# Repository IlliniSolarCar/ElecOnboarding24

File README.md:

# ElecOnboarding25
This is used for Electrical Onboarding for the Fall 2025 Semester

We are very excited to get to work with you guys!

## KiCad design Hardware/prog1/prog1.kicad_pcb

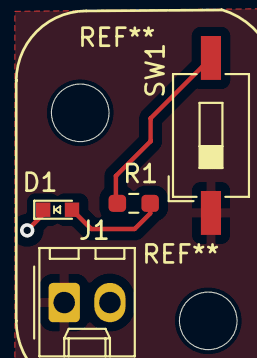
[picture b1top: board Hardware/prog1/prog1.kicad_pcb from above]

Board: 2 copper layers, 4 parts (0 on the bottom side), 4 nets.

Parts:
D1: RED_LED; LED_0603_Symbol_on_F.SilkS
J1: Conn_01x02_Pin; Molex_KK-254_AE-6410-02A_1x02_P2.54mm_Vertical
R1: 105; R_0603_1608Metric_Pad0.98x0.95mm_HandSolder
SW1: SW_Push; SW_DIP_SPSTx01_Slide_6.7x4.1mm_W8.61mm_P2.54mm_LowProfile

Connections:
+3V3: J1.1, SW1.1
GND: D1.1 (K), J1.2
unnamed: D1.2 (A), R1.1
unnamed: R1.2, SW1.2

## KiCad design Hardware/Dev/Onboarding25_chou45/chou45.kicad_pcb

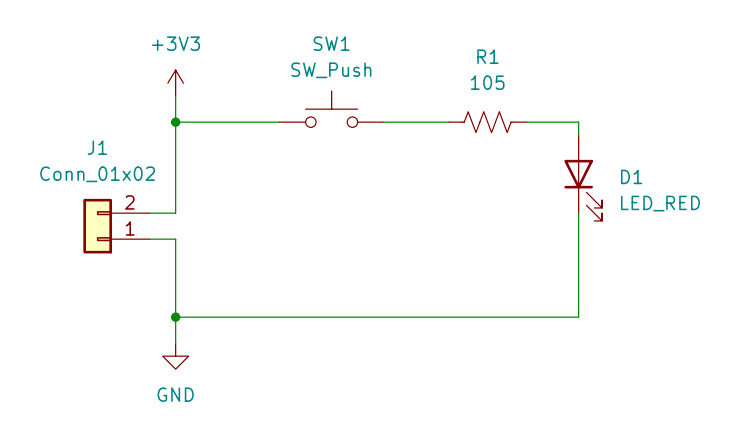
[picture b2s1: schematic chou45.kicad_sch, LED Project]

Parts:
D1: LED_RED; LED_0603_Symbol_on_F.SilkS
J1: Conn_01x02; Molex_KK-254_AE-6410-02A_1x02_P2.54mm_Vertical; MPN 022272021
R1: 105; R_0603_1608Metric_Pad0.98x0.95mm_HandSolder
SW1: SW_Push; SW_DIP_SPSTx01_Slide_6.7x4.1mm_W8.61mm_P2.54mm_LowProfile; MPN 1825910-6

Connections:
+3V3: J1.2, SW1.1
GND: D1.1 (K), J1.1
unnamed: D1.2 (A), R1.2
unnamed: R1.1, SW1.2

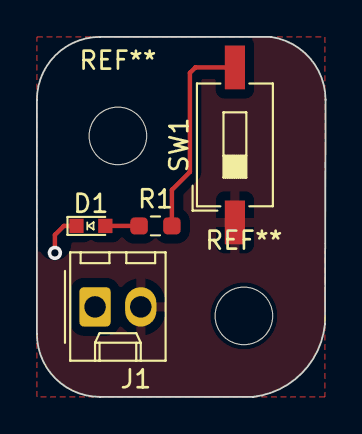
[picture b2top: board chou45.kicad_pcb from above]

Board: 2 copper layers, 16.0 x 20.0 mm, 4 parts (0 on the bottom side), 4 nets.

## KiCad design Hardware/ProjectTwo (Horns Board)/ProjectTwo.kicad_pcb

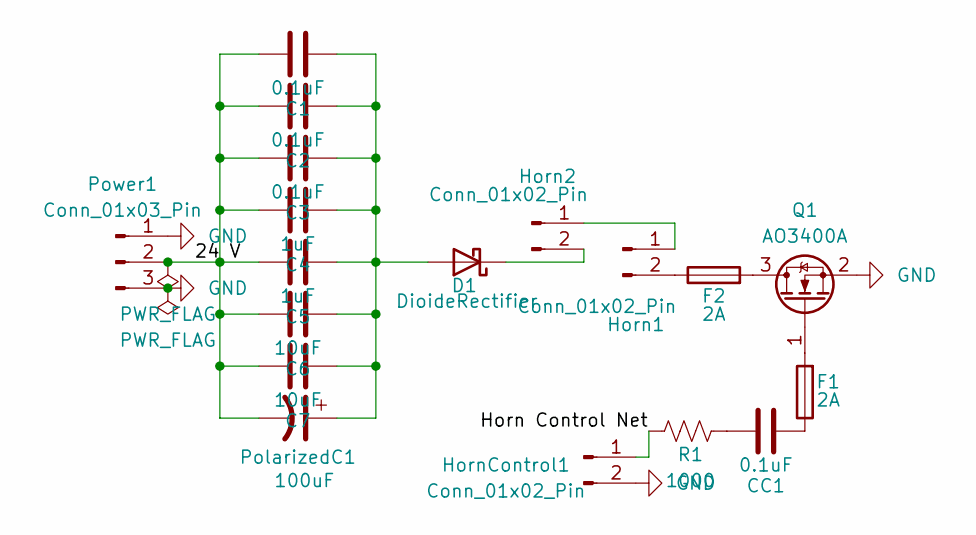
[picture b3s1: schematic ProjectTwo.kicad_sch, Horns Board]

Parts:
C1, C2, C3: 0.1uF; C_1206_3216Metric
C4, C5: 1uF; C_1206_3216Metric
C6, C7: 10uF; C_1206_3216Metric
CC1: 0.1uF; C_1206_3216Metric
D1: DioideRectifier; D_SMA
F1, F2: 2A; Fuse_1206_3216Metric
Horn1, Horn2: Conn_01x02_Pin; TerminalBlock_bornier-2_P5.08mm; MPN CPS-5449-105PM
HornControl1: Conn_01x02_Pin; TerminalBlock_bornier-2_P5.08mm; MPN CPS-5449-105PM
PolarizedC1: 100uF; CP_Radial_D6.3mm_P2.50mm
Power1: Conn_01x03_Pin; TerminalBlock_bornier-3_P5.08mm
Q1: AO3400A; SOT-23; MPN AO3400A
R1: 1000; R_0805_2012Metric

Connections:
/24 V: C1.1, C2.1, C3.1, C4.1, C5.1, C6.1, C7.1, PolarizedC1.2, Power1.2
/Horn Control Net: HornControl1.1, R1.2
GND: HornControl1.2, Power1.1, Power1.3, Q1.2 (S)
unnamed: CC1.1, R1.1
unnamed: CC1.2, F1.1
unnamed: C1.2, C2.2, C3.2, C4.2, C5.2, C6.2, C7.2, D1.2 (A), PolarizedC1.1
unnamed: D1.1 (K), Horn2.2
unnamed: Horn1.1, Horn2.1
unnamed: F2.1, Horn1.2
unnamed: F2.2, Q1.3 (D)
unnamed: F1.2, Q1.1 (G)

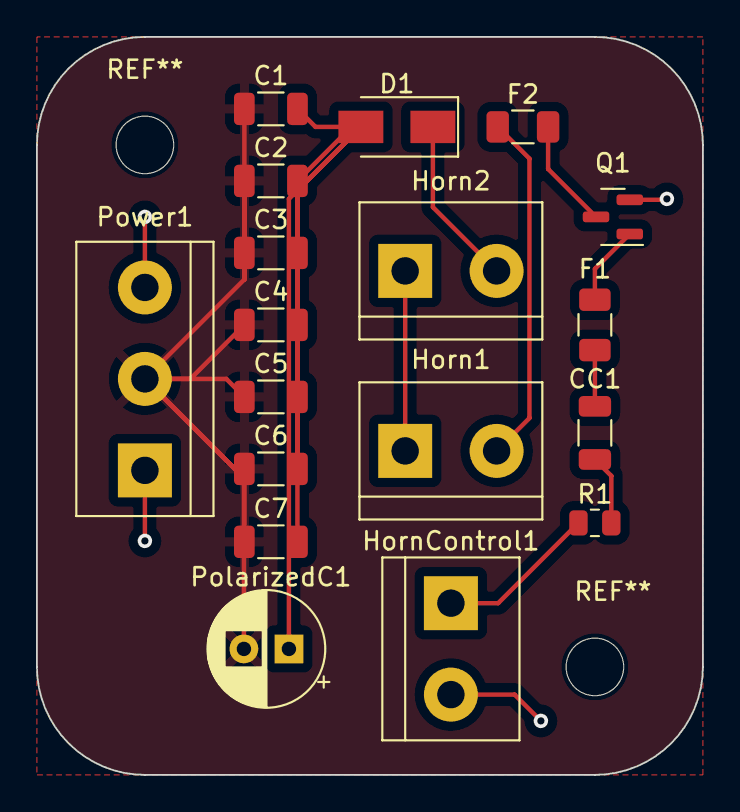
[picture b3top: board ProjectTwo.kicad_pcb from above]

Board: 2 copper layers, 37.0 x 41.0 mm, 18 parts (0 on the bottom side), 11 nets.

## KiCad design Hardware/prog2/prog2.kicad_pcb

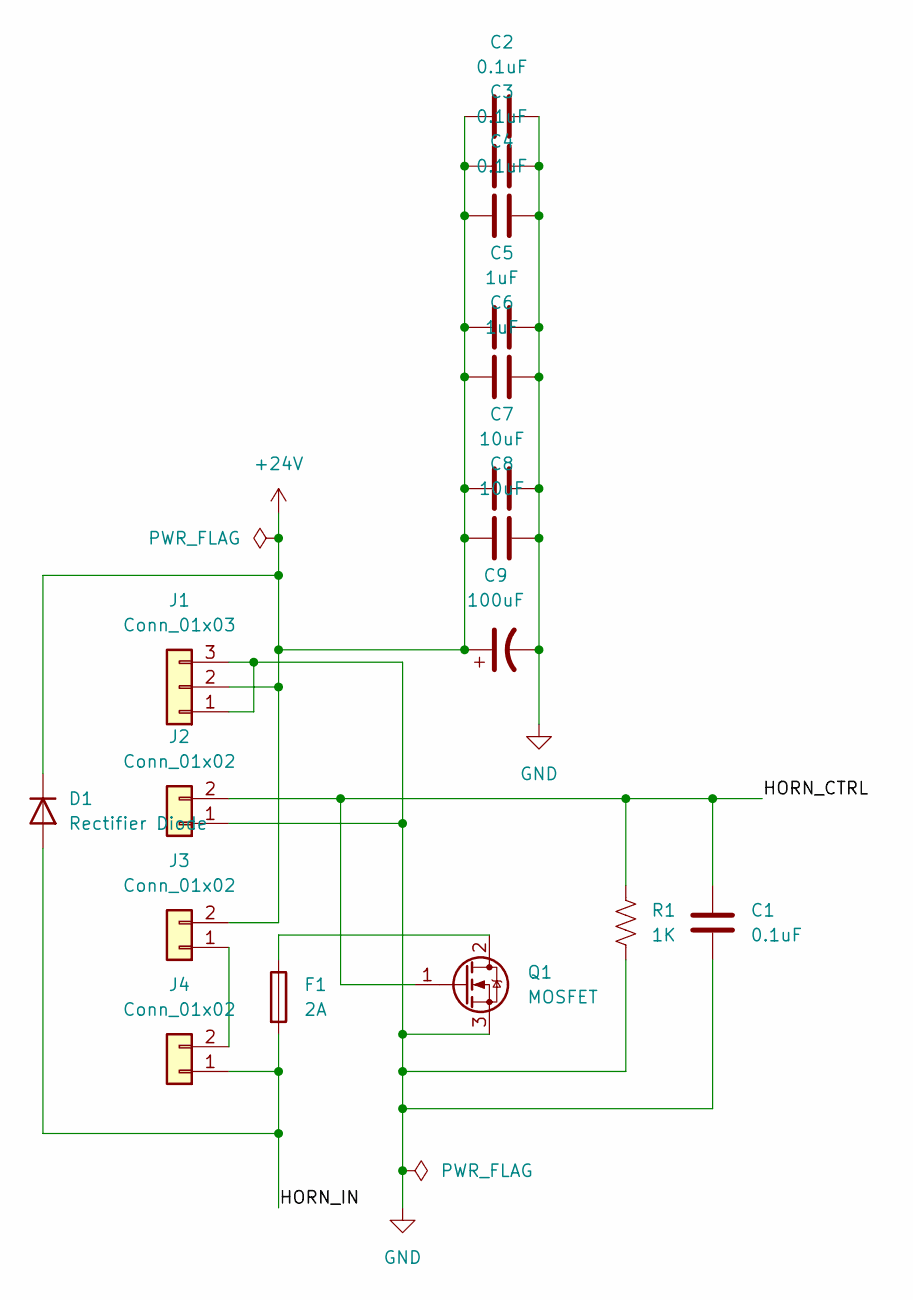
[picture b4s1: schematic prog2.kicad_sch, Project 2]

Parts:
C1, C2, C3, C4: 0.1uF; C_0201_0603Metric_Pad0.64x0.40mm_HandSolder
C5, C6: 1uF; C_0402_1005Metric_Pad0.74x0.62mm_HandSolder
C7, C8: 10uF; C_0504_1310Metric_Pad0.83x1.28mm_HandSolder
C9: 100uF; C_0805_2012Metric_Pad1.18x1.45mm_HandSolder
D1: Rectifier Diode; D_SMA; MPN US2DA
F1: 2A; Fuse_0603_1608Metric_Pad1.05x0.95mm_HandSolder
J1: Conn_01x03; Molex_Micro-Fit_3.0_43650-0300_1x03_P3.00mm_Horizontal; MPN 436500300
J2, J3, J4: Conn_01x02; Molex_Micro-Fit_3.0_43650-0210_1x02-1MP_P3.00mm_Horizontal; MPN 022272021
Q1: MOSFET; TO-252-2; MPN STD7NK40Z
R1: 1K; R_0603_1608Metric_Pad0.98x0.95mm_HandSolder

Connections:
+24V: C2.1, C3.2, C4.1, C5.1, C6.1, C7.1, C8.1, C9.1, D1.1 (K), J1.2, J3.2
/HORN_CTRL: C1.2, J2.2, Q1.1 (G), R1.2
/HORN_IN: D1.2 (A), F1.2, J4.1
GND: C1.1, C2.2, C3.1, C4.2, C5.2, C6.2, C7.2, C8.2, C9.2, J1.1, J1.3, J2.1, Q1.3 (S), R1.1
unnamed: J3.1, J4.2
unnamed: F1.1, Q1.2 (D)

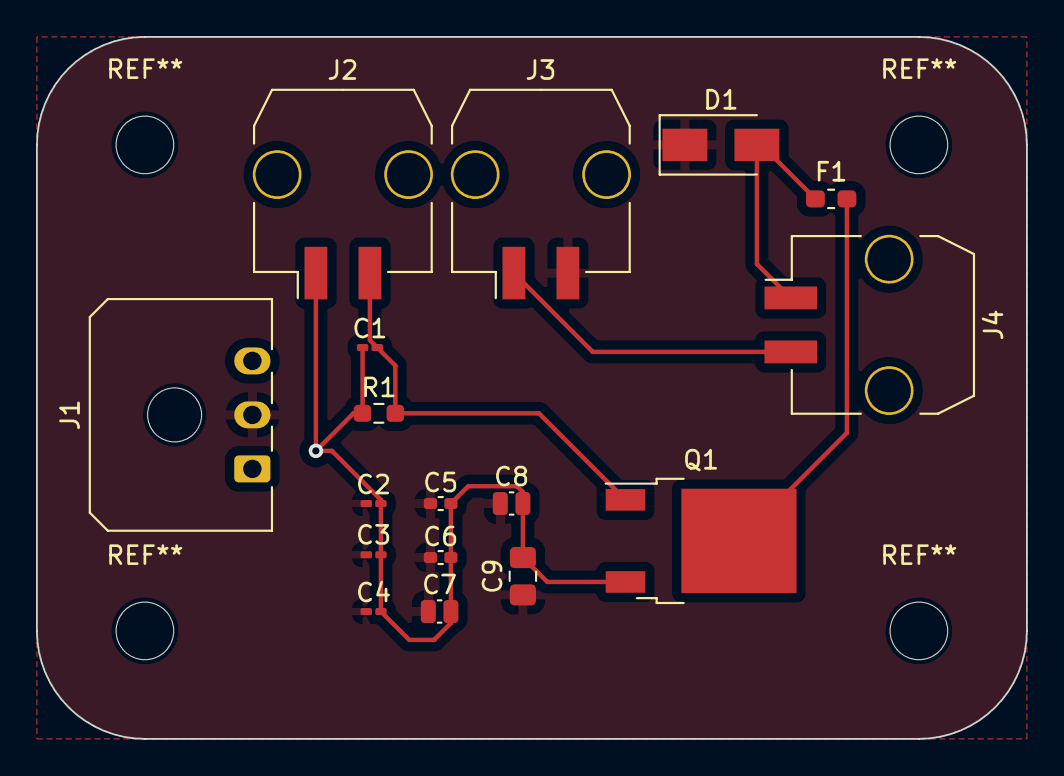
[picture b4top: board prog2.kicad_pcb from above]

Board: 2 copper layers, 55.0 x 39.0 mm, 17 parts (0 on the bottom side), 6 nets.

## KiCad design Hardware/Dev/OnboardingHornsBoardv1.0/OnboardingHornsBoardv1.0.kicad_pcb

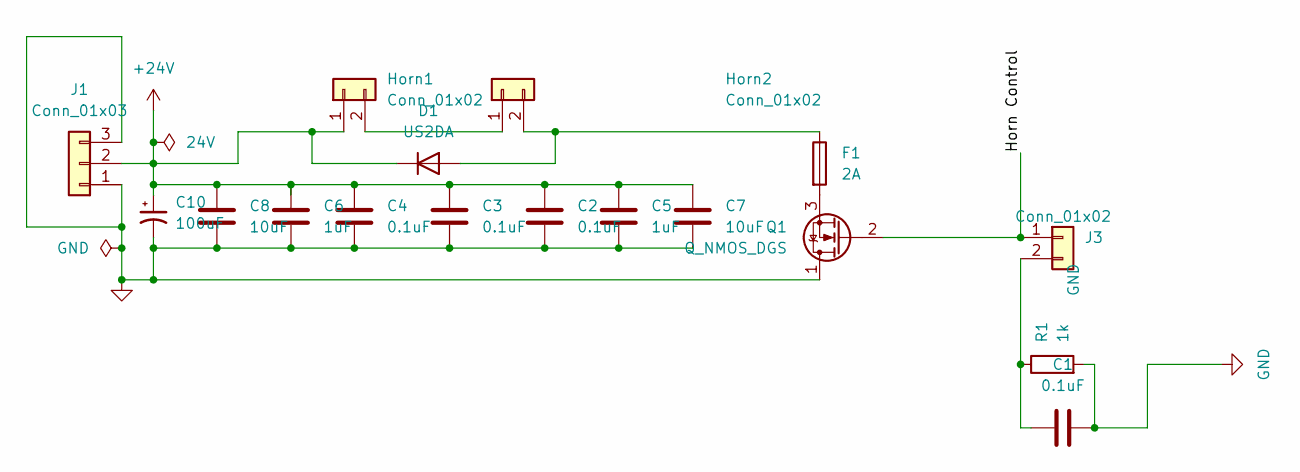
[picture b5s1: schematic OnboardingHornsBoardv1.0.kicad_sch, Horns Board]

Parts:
C1, C2, C3, C4: 0.1uF; C_0603_1608Metric
C5, C6: 1uF; C_0603_1608Metric
C7, C8: 10uF; C_0603_1608Metric
C10: 100uF; C_0603_1608Metric
D1: US2DA; D_SMA
F1: 2A; Fuse_0402_1005Metric
Horn1, Horn2: Conn_01x02; Molex_Micro-Fit_3.0_43650-0200_1x02_P3.00mm_Horizontal
J1: Conn_01x03; Molex_Micro-Fit_3.0_43650-0300_1x03_P3.00mm_Horizontal
J3: Conn_01x02; Molex_Micro-Fit_3.0_43650-0200_1x02_P3.00mm_Horizontal
Q1: Q_NMOS_DGS; TO-252-2
R1: 1k; R_0603_1608Metric

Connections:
+24V: C2.1, C3.1, C4.1, C5.1, C6.1, C7.1, C8.1, C10.1, D1.1 (K), Horn1.1, J1.2
/Horn Control: J3.1, Q1.2 (G)
GND: C1.2, C2.2, C3.2, C4.2, C5.2, C6.2, C7.2, C8.2, C10.2, J1.1, J1.3, Q1.1 (D), R1.2
unnamed: D1.2 (A), F1.1, Horn2.2
unnamed: Horn1.2, Horn2.1
unnamed: C1.1, J3.2, R1.1
unnamed: F1.2, Q1.3 (S)

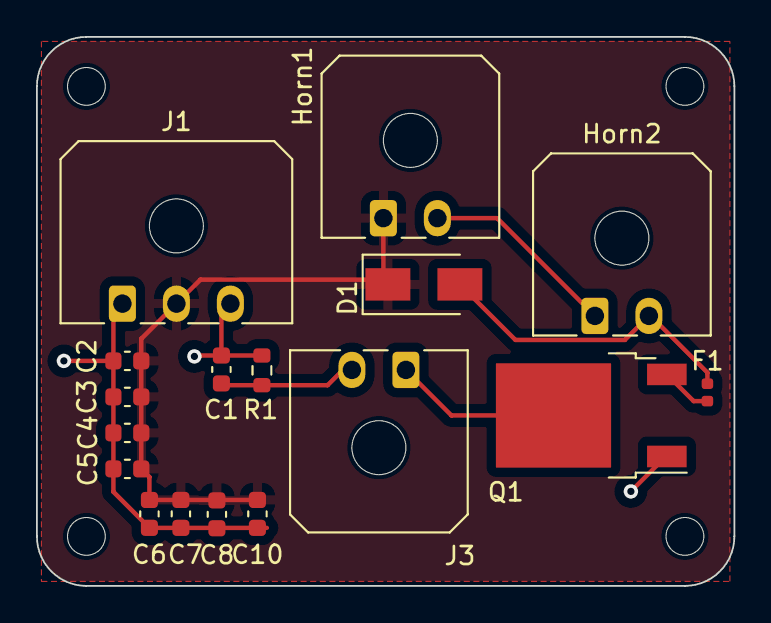
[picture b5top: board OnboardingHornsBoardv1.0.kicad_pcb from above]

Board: 2 copper layers, 38.8 x 30.5 mm, 17 parts (0 on the bottom side), 7 nets.

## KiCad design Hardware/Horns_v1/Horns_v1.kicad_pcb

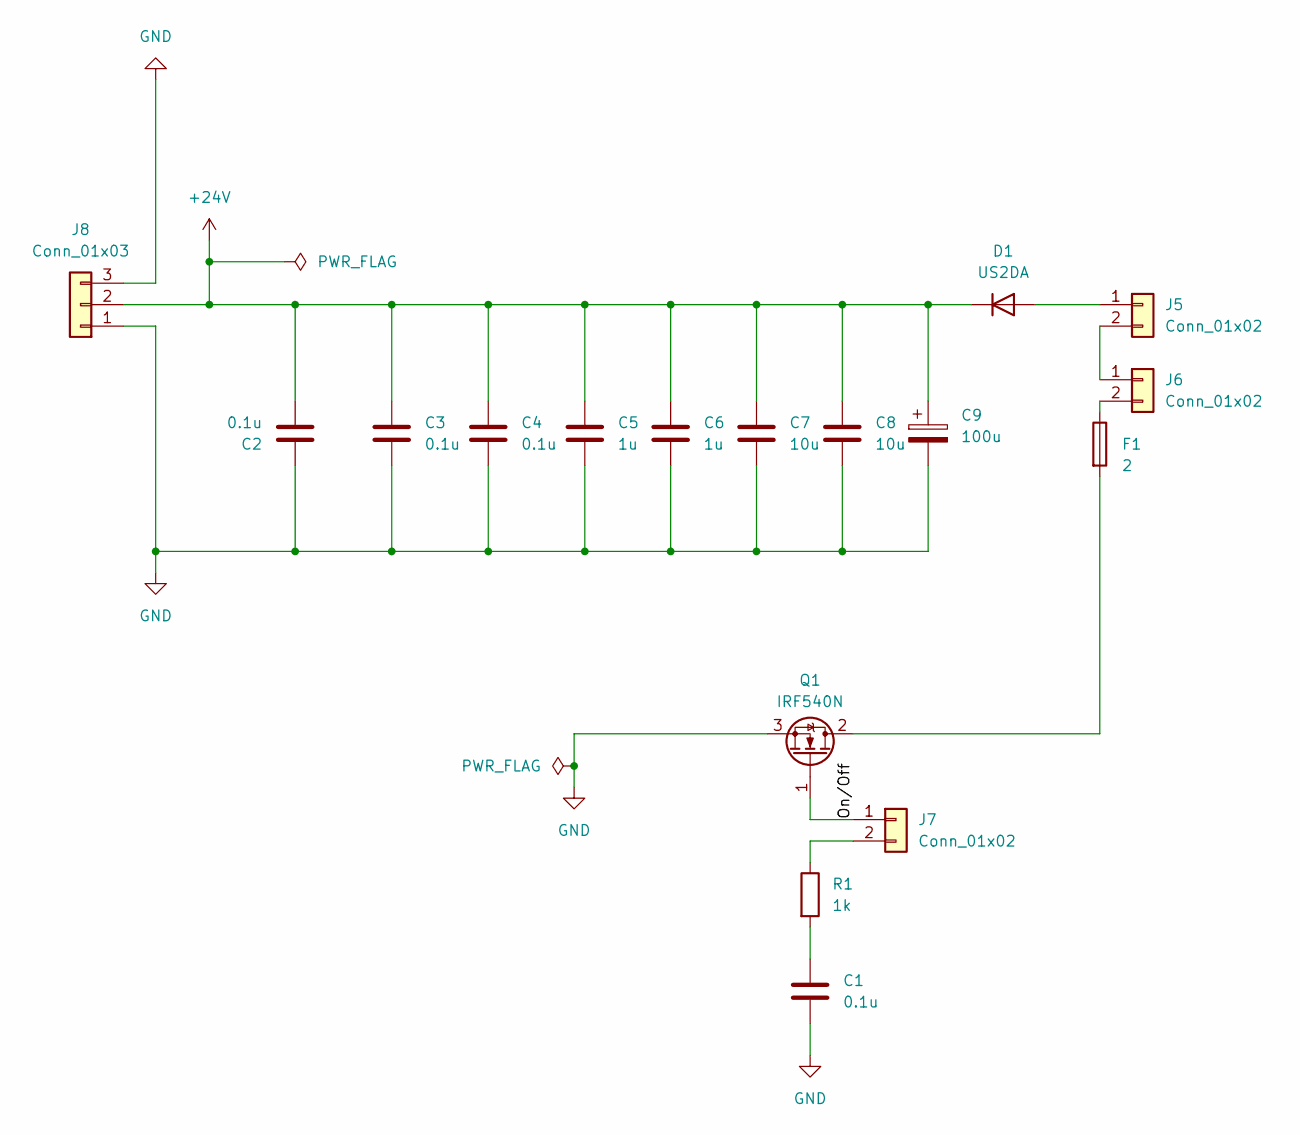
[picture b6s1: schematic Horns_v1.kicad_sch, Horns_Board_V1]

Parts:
C1, C2, C3, C4: 0.1u; CP_Radial_D5.0mm_P2.00mm
C5, C6: 1u; CP_Radial_D5.0mm_P2.00mm
C7, C8: 10u; CP_Radial_D5.0mm_P2.00mm
C9: 100u; CP_Radial_D5.0mm_P2.00mm
D1: US2DA; D_SMA
F1: 2; Fuse_0603_1608Metric_Pad1.05x0.95mm_HandSolder
J5, J6, J7: Conn_01x02; Molex_KK-254_AE-6410-02A_1x02_P2.54mm_Vertical
J8: Conn_01x03; Molex_KK-254_AE-6410-03A_1x03_P2.54mm_Vertical
Q1: IRF540N; TO-220-3_Vertical
R1: 1k; R_0603_1608Metric_Pad0.98x0.95mm_HandSolder

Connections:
+24V: C2.1, C3.1, C4.1, C5.1, C6.1, C7.1, C8.1, C9.1, D1.1 (K), J8.2
/On/Off: J7.1, Q1.1 (G)
GND: C1.2, C2.2, C3.2, C4.2, C5.2, C6.2, C7.2, C8.2, C9.2, J8.1, J8.3, Q1.3 (S)
unnamed: C1.1, R1.2
unnamed: D1.2 (A), J5.1
unnamed: J5.2, J6.1
unnamed: F1.1, J6.2
unnamed: J7.2, R1.1
unnamed: F1.2, Q1.2 (D)

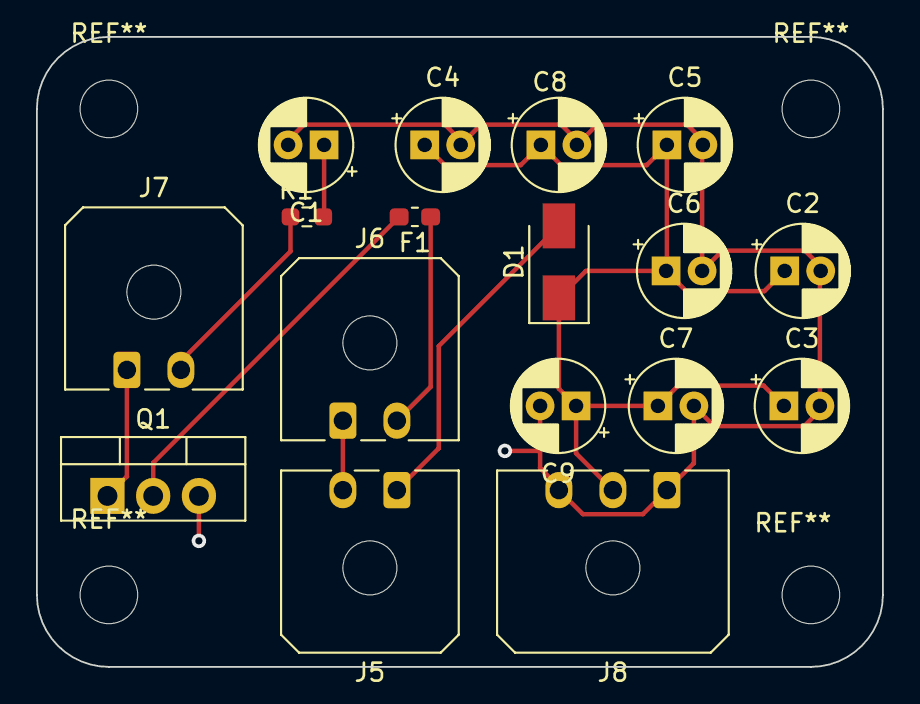
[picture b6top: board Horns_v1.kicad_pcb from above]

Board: 2 copper layers, 47.0 x 35.0 mm, 17 parts (0 on the bottom side), 9 nets.

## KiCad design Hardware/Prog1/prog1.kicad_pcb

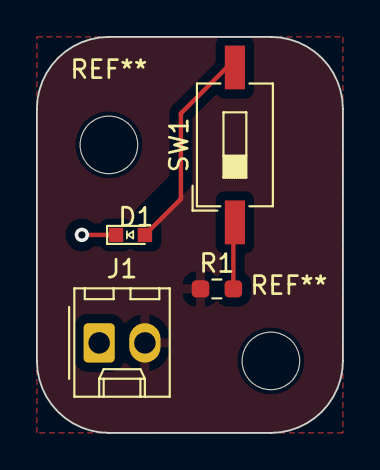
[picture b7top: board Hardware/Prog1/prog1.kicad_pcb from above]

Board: 2 copper layers, 17.0 x 22.0 mm, 4 parts (0 on the bottom side), 4 nets.

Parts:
D1: LED_RED; LED_0603_Symbol_on_F.SilkS
J1: Conn_01x02; Molex_KK-254_AE-6410-02A_1x02_P2.54mm_Vertical
R1: R_US; R_0603_1608Metric_Pad0.98x0.95mm_HandSolder
SW1: SW_Push; SW_DIP_SPSTx01_Slide_6.7x4.1mm_W8.61mm_P2.54mm_LowProfile

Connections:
+3V3: J1.2, R1.1
GND: D1.1 (K), J1.1
unnamed: D1.2 (A), SW1.2
unnamed: R1.2, SW1.1

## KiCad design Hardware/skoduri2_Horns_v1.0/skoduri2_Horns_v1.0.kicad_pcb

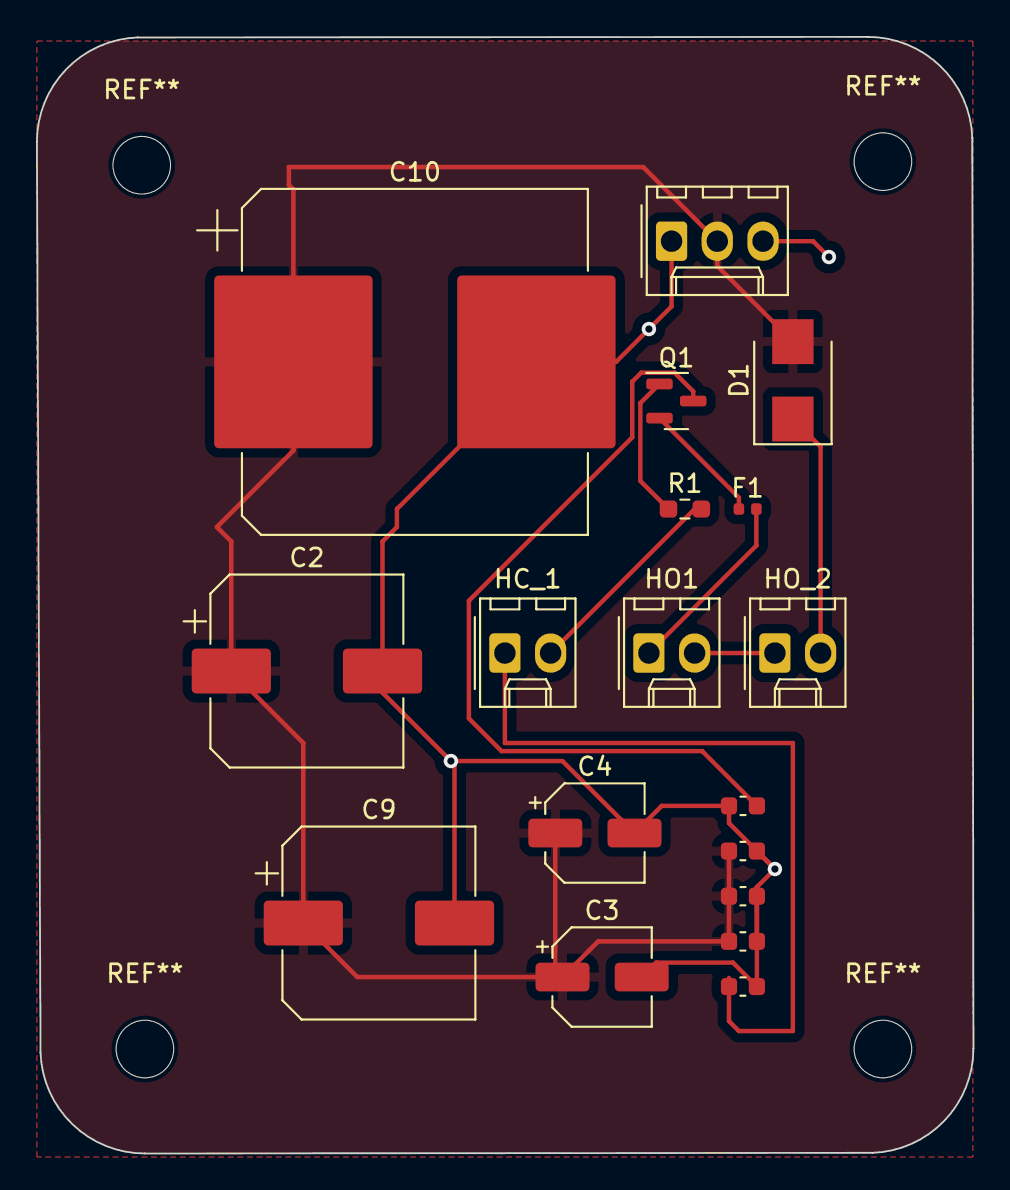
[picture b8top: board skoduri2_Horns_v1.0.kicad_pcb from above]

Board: 2 copper layers, 52.0 x 62.0 mm, 18 parts (0 on the bottom side), 10 nets.

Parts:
C1: 0.1Fµ; C_0603_1608Metric
C2, C9: 10µF; CP_Elec_10x10.5
C3, C4: 1µF; CP_Elec_5x4.5
C5, C6, C8: 0.1µF; C_0603_1608Metric
C7: 0.1µ; C_0603_1608Metric
C10: 100µF; CP_Elec_18x22
D1: S2JTR; D_SMB
F1: 2A; Fuse_0402_1005Metric
HC_1: Conn_01x02; Molex_KK-254_AE-6410-02A_1x02_P2.54mm_Vertical
HO1: Conn_01x02; Molex_KK-254_AE-6410-02A_1x02_P2.54mm_Vertical
HO_2: Conn_01x02; Molex_KK-254_AE-6410-02A_1x02_P2.54mm_Vertical
Power1: Conn_01x03; Molex_KK-254_AE-6410-03A_1x03_P2.54mm_Vertical
Q1: Q_NMOS_GDS; SOT-23
R1: 1kΩ; R_0603_1608Metric_Pad0.98x0.95mm_HandSolder

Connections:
+24V: C2.1, C3.1, C4.1, C5.1, C6.1, C7.1, C9.1, C10.1, D1.2 (A), Power1.2
GND: C1.1, C2.2, C3.2, C4.2, C5.2, C6.2, C7.2, C8.2, C9.2, C10.2, Power1.1, Power1.3
unnamed: D1.1 (K), HO_2.2
unnamed: C8.1, HC_1.1
unnamed: HC_1.2, R1.2
unnamed: F1.2, HO1.1
unnamed: HO1.2, HO_2.1
unnamed: F1.1, Q1.2 (D)
unnamed: Q1.1 (G), R1.1
unnamed: C1.2, Q1.3 (S)

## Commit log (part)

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2023-09-26 Hardware Advanced Project Completion
2023-09-26 draft
2023-09-26 Spec Sheet for Horn
2023-09-26 [Firmware project 1 completed]
2023-09-26 added first version of day_3 lesson
2023-09-26 firmware project 2, looking for feedback
2023-09-26 Finished LED project
2023-09-26 horns_v.1.0 schematic done
2023-09-27 added footprints to schematic
2023-09-27 Horns_v1.0 PCB Design completed
2023-09-27 rachel28 hardware project 1 complete
2023-09-27 Hardware Project 2 Complete
2023-09-27 Firmware project
2023-09-27 finished project 1 firmware
2023-09-27 reworked hornsBoard PCB
2023-09-27 Finished firmware project 1
2023-09-27 finished firmware 1
2023-09-27 aakarsh garg onboarding
2023-09-27 firmware 1
2023-09-28 included updates to main.cpp for firmware
2023-09-28 revised firmware 2
2023-09-28 finished firmware1
2023-09-28 Firmware Project 2: Potentiometer Blink Rate
2023-09-28 finished hardware project 1
2023-09-28 Proj 1
2023-09-28 Finished firmware project 2
2023-09-28 finished project 2
2023-09-28 Edited specs file for Horn project
2023-09-28 Michael's LED Onboarding Project Complete
2023-09-28 Horn Schematic Completed
2023-09-28 Firmware Project 2 attempt
2023-09-29 abhi kadiam project 1 complete
2023-09-29 schematic for Hardware project 2
2023-09-29 Anjalit3 hardware project 1 complete
2023-09-29 LED done
2023-09-30 Added layout for hardware project 2
2023-09-30 Gerber Files
2023-09-30 Actually added the gerber files this time:)
2023-09-30 did advanced firmware to the best of my knowledge
2023-09-30 added adv hardware
2023-09-30 not sure
2023-09-30 Added features described in LED_Project.md to LED_Project.sch
2023-09-30 Added features described in Horn spec file to schematic file
2023-09-30 Firmware project 1 done
2023-09-30 firmware project 1
2023-09-30 updated firmware for onboarding project 2 solution
2023-09-30 Firmware Project 2 complete
2023-09-30 Firmware project 2
2023-09-30 firmware p2
2023-09-30 Designed Layout, made changes to 'emreta2_Horn.md' in the test points section, added three test points that were not in the schematic.
2023-10-02 Fixed the name of InstantDFM report
2023-10-02 pushing horn folder
2023-10-02 Specs
2023-10-02 finished project 2 FW
2023-10-02 1st firmware project
2023-10-03 hardware hard
2024-02-29 kadjfkls
2024-02-29 alkdjklajf
2024-03-02 Project 1: LED Circuit
2024-03-02 Project 1: Heartbeat Completion - Please Check My Work
2024-09-12 Layout Started
2024-09-13 Project 1
    Completed Project 1 (LED)
2024-09-15 bz22 Led Circuit
2024-09-15 done with prog1
2024-09-15 Update .gitignore
    ignoring .ick now
2024-09-16 test
2024-09-16 super hard first project led pcb
2024-09-16 first hardware project
2024-09-17 added data sheet
2024-09-17 Nearly finish LED project
2024-09-17 done wiht prog1
2024-09-17 Merged changes from origin.
2024-09-17 Fix clearance error by changing clearance constraints
2024-09-17 calumnd2 project 1 complete
2024-09-17 fix power flag
2024-09-17 testing to see if I can add folders now that i have removed myself as admin
2024-09-17 starting project 1
2024-09-17 LED_Project
2024-09-17 LED PCB Project
2024-09-18 temp push
2024-09-19 hello
2024-09-19 Test for Push
2024-09-19 i did stuff
2024-09-19 work in progress!
2024-09-19 anything
2024-09-19 team arthur project 1 complete
2024-09-19 asdf
2024-09-19 haha
2024-09-19 Camille Woods finished LED Project
2024-09-19 trial
2024-09-19 Started LED project
2024-09-19 finished project 1!
2024-09-19 LED Circuit Done
2024-09-20 LED Project finished
2024-09-21 ledproject
2024-09-22 philipc6
2024-09-22 Onboarding LED complete
2024-09-22 Heartbeat Project
2024-09-22 LED Project 1
2024-09-22 Siraphat Project 1 LED Complete
2024-09-23 Yutian Chen LED Project complete
2024-09-23 Michael Torres LED Project 1 Complete
2024-09-23 Chansey2 project 1 complete
2024-09-23 LED Project Done
2024-09-23 Project 1 LED completed by Matthew Gu (mgu11)
2024-09-23 adding first prog1
2024-09-23 [LED Project Onboarding Adam Kaszok]
2024-09-23 LED Onboarding Project Done
2024-09-23 LED complete
2024-09-23 Abhay Pokhriyal finished LED Project
2024-09-23 David Chen project 1 complete
2024-09-23 Completed Firmware Intro Project
2024-09-24 proj1 updated
2024-09-24 Horns Board Done
2024-09-24 Completed hardware project 1
2024-09-24 finished hardware task 1, copied template for horn
2024-09-24 Robert Childs Project 1 complete
2024-09-24 Finished Hardware Onboarding 1
2024-09-24 finished led blink firmware
2024-09-24 Kevin Zhang first onboarding hardware project
2024-09-25 Hardware Project 1
2024-09-25 hardware project done
2024-09-25 1st hardware project done
2024-09-26 LED Project - Rishi Deshpande, user: Rishisd2
2024-09-26 Quan Yuan project 1 complete
2024-09-26 calumnd2 horns board specs
2024-09-26 firmware task 1 complete, untested due to lack of board
2024-09-26 updated hardware
2024-09-26 Finished with heartbeat firmware project!
2024-09-26 Completed first firmware project.
2024-09-26 Completed LED Project 1
2024-09-26 Some edits were made to the PCB board components layout. - Eunsol
2024-09-26 Please review my updated PCB LED and my Firware Heartbeat Project.
2024-09-26 Finished Hardware/Firmware first projects
2024-09-28 Firmware Potentiometer Project
2024-09-30 calumnd2 horns board layout
2024-09-30 finished prog1 layout
2024-09-30 project 1 led completed
2024-09-30 Finished project 1
2024-09-30 Added trace connection to ground via
2024-09-30 Updated the 90 degree traces to have 2 45 degree turns instead. Couldn't figure out how to rename the files easily.
2024-10-01 Completed Project 1
2024-10-01 firmware project 1 complete, dunno if hardware project 1 was checked
2024-10-01 My first firmware Onboarding Project (Blinking LED)
2024-10-01 ch110 hardware project complete
2024-10-01 Finished firmware project 2.
2024-10-01 ch110 firmware project complete
2024-10-01 fixed firmware 1
2024-10-01 calumnd2 horns board gerbers & dfm
2024-10-01 Finished firmware project 2git statusgit statusgit status
2024-10-01 done with prog 2
2024-10-01 Updated firmware project and completed
2024-10-01 updated firmware project complete
2024-10-01 done with firmware
2024-10-01 LED blink finished
2024-10-01 firmware proj 1
2024-10-01 Finished Firmware projects 1 & 2
2024-10-01 Firwmare Easy Project Done
2024-10-01 Project 1 LED
2024-10-01 [Project 1]
2024-10-01 Finished project 1 firmware.
2024-10-01 onboarding project 1 complete
2024-10-01 updated project1 done
2024-10-01 Ritvik Annadi Project 1 Finished
2024-10-02 finished hardware prject 1
2024-10-02 finished hardware porject 1
2024-10-02 Finished potentiometer firmware project
2024-10-02 updated firmware project 1
2024-10-02 more project 1 firmware changes
2024-10-02 specs file somewhat edited
2024-10-02 added a few components
2024-10-02 Finished onboarding; forgot to commit until now.
2024-10-03 done
2024-10-03 did project 2 and 1 for firmware
2024-10-03 Completed Easy Hardware, Easy and Advanced Firmware
2024-10-03 Sachith Onboarding
2024-10-03 finished hardware project
2024-10-03 finished hardware 2 and firmware 1
2024-10-03 firmware project 1 and 2
2024-10-03 in prog
2024-10-03 Firmware 1 and 2
2024-10-03 Firmware Projects1 & 2
2024-10-03 finished hardware project led
2024-10-03 firmware project 1 commit
2024-10-03 firmware and hardware push
2024-10-03 firmware1
2024-10-03 Spec sheet for Horns Board
2024-10-03 firmware easy project done
2024-10-03 hardware easy project done
2024-10-03 firmware project 2 done
2024-10-04 finished schematic for project 2
2024-10-04 Firmware Project 2 Completed
2024-10-05 proj 2
2024-10-05 completed circuit schematic
2024-10-05 firmwareproject2
2024-10-05 correct and finished firmware project 1
2024-10-05 Firmware, challenge project
2024-10-05 Finished Horns Board Project
2024-10-05 finish project 1 and 2
2024-10-05 edit LED footprint
2024-10-06 project 1 and 2 firmware completed
2024-10-06 Firmware Easy finished
2024-10-06 moving hardware files to ./hardware
2024-10-06 Fix unnecessary wire bends on hardware traces
2024-10-06 I tried to add the projects again, so hopefully it worked this time.
2024-10-06 Fixed firmware project 1 code
2024-10-06 firmware hard project 2 commit
2024-10-06 Firmware
2024-10-06 firmware project 1 & 2
2024-10-06 hardware challenge project push
2024-10-06 project 2
    project 2
2024-10-07 led proj and firm projects 1 and 2
2024-10-07 [firmware project 1 update]
2024-10-07 Completed schematic/pcb for onboarding, -Elias
2024-10-07 firmware proj1 done
2024-10-07 firmware proj2 done
2024-10-07 LED Project completed
2024-10-07 finished layout and Instant DFM Report
2024-10-07 Fixed traces angles, may not have found them all though
2024-10-07 updated project 1 files
2024-10-07 Firmware project finished
2024-10-07 Advanced software project finished
2024-10-07 code deleted for some reason, had to redo but hopefully this works (this is firmware project 1 and 2)
2024-10-07 finished firmware project
2024-10-07 Firmware project finished again
2024-10-07 Fixed LED ground connection & started second Firmware project
2024-10-07 fixed bugs
2024-10-07 LED ground connection tweak
2024-10-07 Add files via upload
    led project
2024-10-07 relocated LED project
2024-10-07 finished easy + hard firmware projects
2024-10-07 saved pins.h
2024-10-07 Fixed FW 2
2024-10-07 Third try's the charm, Firmware 1 and 2 (I just want to join why is Git like this)
2024-10-07 Traces fixed for both hardware
2024-10-07 Firmware Projects 1 and 2 finished
2024-10-07 hardware 2
2024-10-07 hardware 2 schematic
2024-10-07 firmware project 2 completed in project 1 folder
2024-10-07 hardware 2, not sure how to fix errors in DFM
2024-10-07 saved
2024-10-07 modified: .cproject modified: src/main.cpp ../../Hardware/Horn Project/ ../../Hardware/prog 1/LED prog1.kicad_pro ../../Hardware/prog 1/Title_Block.kicad_wks ../../Hardware/prog 1/fp-lib-table ../../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
2024-10-07 hardware project completed
2024-10-07 Made some changes.
2024-10-07 Vikram Iyer Hardware project complete
2024-10-07 Add files via upload
    LED Circuit
2024-10-07 Added files via upload
2024-10-08 Completed Hardware Project 1: LED Circuit
2024-10-08 new file: Horn.kicad_pcb new file: Horn.kicad_pro Horn.kicad_sch Horn.md Title_Block.kicad_wks fp-lib-table
2024-10-08 Pushing Firmware
2024-10-08 first project
2024-10-08 first firmware project complete
2024-10-08 firmware project 1&2
2024-10-08 Firmware projects 1 and 2 completed
2024-10-08 Completed Firmware Project 1: Heartbeat
2024-10-08 Quan Yuan Firmware Project1&2 complete
2024-10-08 Completed Firmware Project 2: Potentiometer Blink Rate
2024-10-08 Fixed an error in firmware
2024-10-08 Finished Firmware Project2
2024-10-08 Advanced firmware project complete
2024-10-08 Fixed firmware project 2
2024-10-08 project 1 hardware projects 1 and 2 firmware complete
2024-10-08 led project...had issues with git
2024-10-08 both firmware...had trouble with main.cpp...also git
2024-10-08 Horn project
2024-10-09 This is all firware
2024-10-09 This is all firmware
2024-10-09 completed firmware project 1 and 2
2024-10-09 completed firmware projects 1 and 2
2024-10-09 Firmware Project 1: Heartbeat
    did suggested method & alternative method for blinking LED
2024-10-09 firmware challenge proj: potentiometer
    potentiometer variable resistance for variable blink rate of LED
2024-10-09 Firmware projects 1 and 2
2024-10-09 firmware 1 and 2, hardware 1
2024-10-09 final push
2024-10-09 finish projects
2024-10-09 fixed up hw1 and fw1
2024-10-09 I finished the two firmware projects, Yipeegit status
2024-10-09 firmware project#3 finished
2024-10-09 added modified file to project#3
2024-10-10 changed files
2024-10-10 changed variable name for test
2024-10-10 submit the 1st firmware project
2024-10-10 Firmware Project 2 finished
2024-10-10 Finish Project 2 Firmware
2024-10-10 Added hardware project 2
2024-10-10 Project 1 Hardware I couldn't figure out why filled zone is not connected.
2024-10-10 Added easy hardware project
2024-10-10 onboarding projects done
2024-10-11 Madhumita Manthri firmware project 2
    Hello! I tried pushing it from terminal but it kept giving me authentication error. Therefore I am trying my level best to update changes through my branch.
2024-10-14 Hardware Project fixes
